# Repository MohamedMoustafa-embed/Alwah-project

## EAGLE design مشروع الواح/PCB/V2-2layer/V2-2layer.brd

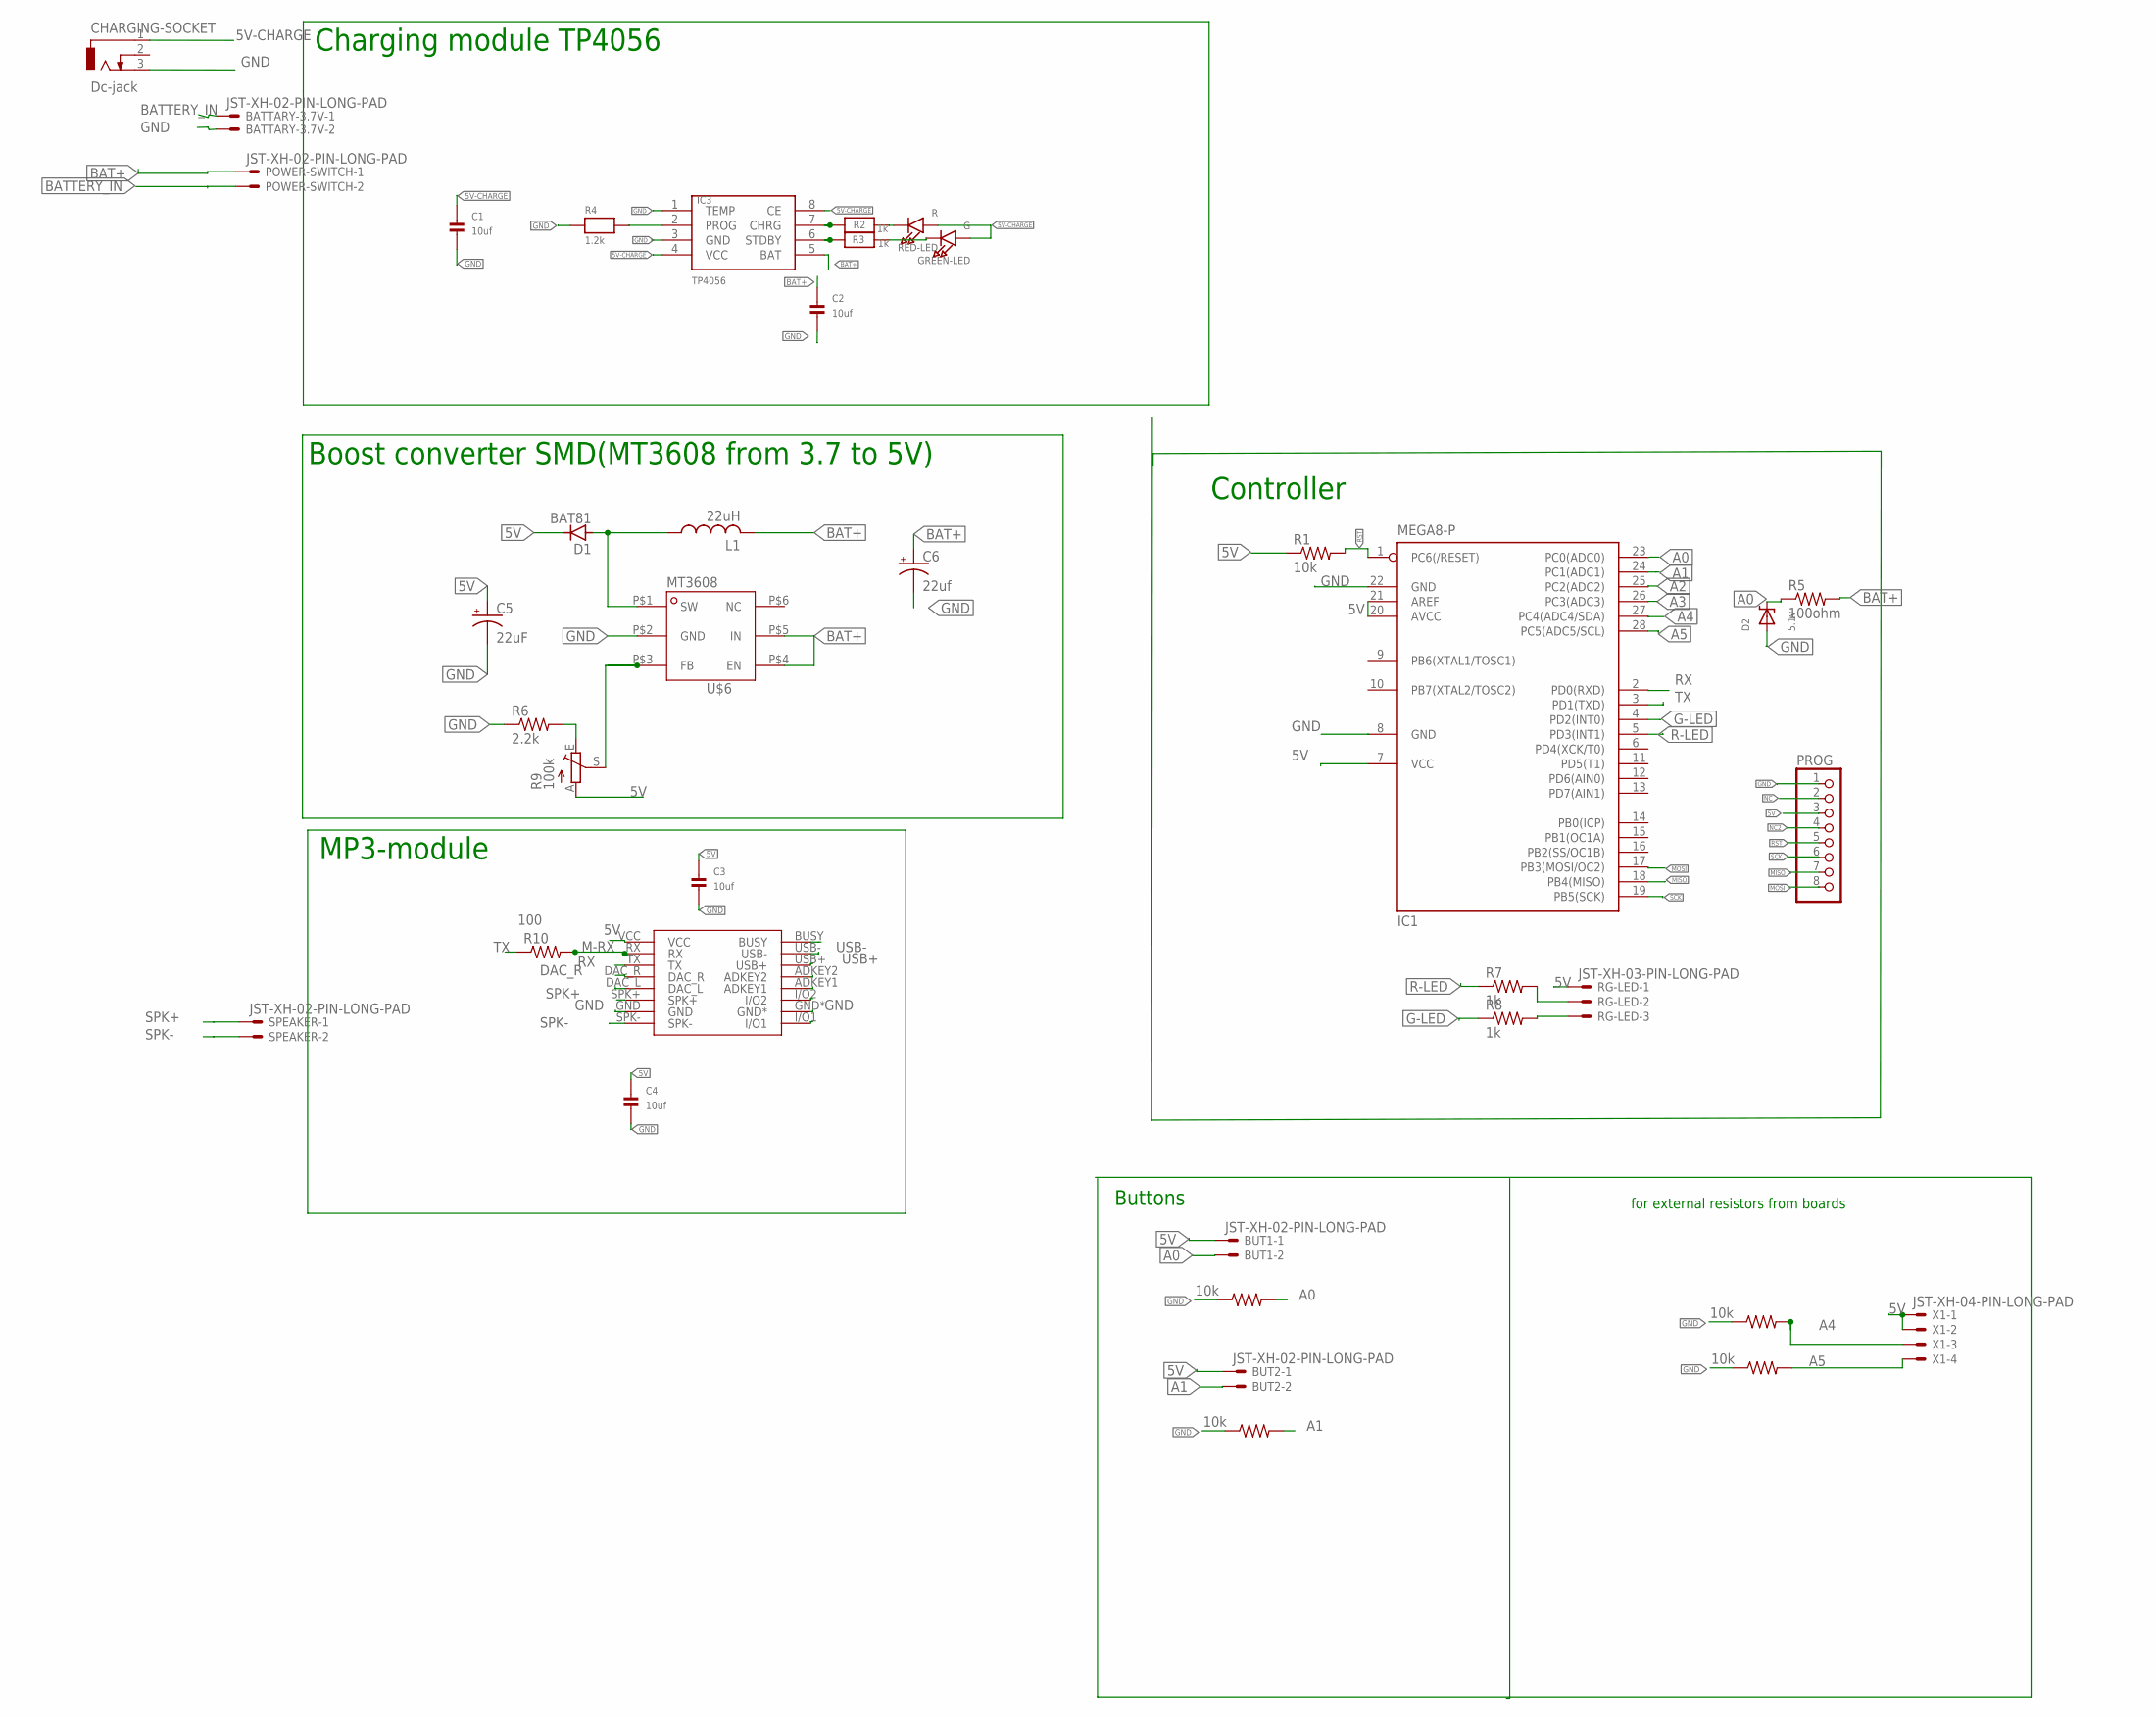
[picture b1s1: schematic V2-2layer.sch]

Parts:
BATTARY-3.7V: JST-XH-02-PIN-LONG-PAD; JST-XH-02-PACKAGE-LONG-PAD
BUT1, BUT2: JST-XH-02-PIN-LONG-PAD; JST-XH-02-PACKAGE-LONG-PAD
C1, C2, C3, C4: 10uf; 0805
C5: 22uF; E2,5-6E
C6: 22uf; E2,5-6E
CHARGING-SOCKET: Dc-jack; DCJ0303
D1: BAT81; DO34-7
D2: 5.1v; SMADIODE
GREEN-LED: G; CHIPLED_0805
IC1: MEGA8-P; DIL28-3
IC3: TP4056; SOP-8
KEYPADS, KEYPADS1, KEYPADS2, KEYPADS3: 10k; 0204/7
L1: 22uH; L1812
POWER-SWITCH: JST-XH-02-PIN-LONG-PAD; JST-XH-02-PACKAGE-LONG-PAD
PROG: PINHD-1X8; 1X08
R1: 10k; 0204/7
R2, R3: 1k; _0805
R4: 1.2k; _0805
R5: 100ohm; 0204/7
R6: 2.2k; M0805
R7, R8: 1k; 0204/7
R9: 100k; B25U
R10: 100; 0204/7
RED-LED: R; CHIPLED_0805
RG-LED: JST-XH-03-PIN-LONG-PAD; JST-XH-03-PACKAGE-LONG-PAD
SPEAKER: JST-XH-02-PIN-LONG-PAD; JST-XH-02-PACKAGE-LONG-PAD
U$2: MP3_MODULE
U$6: MT3608SOT23-6; SOT23-6
X1: JST-XH-04-PIN-LONG-PAD; JST-XH-04-PACKAGE-LONG-PAD

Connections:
5V: BUT1.1, BUT2.1, C3.1, C4.1, C5.+, D1.C, IC1.7 (VCC), IC1.20 (AVCC), IC1.21 (AREF), PROG.3, R1.1, R9.A, RG-LED.1, U$2.VCC, X1.1, X1.2
5V-CHARGE: C1.1, CHARGING-SOCKET.1, GREEN-LED.A, IC3.4 (VCC), IC3.8 (CE), RED-LED.A
A0: BUT1.2, D2.C, IC1.23 (PC0(ADC0)), KEYPADS.2, R5.1
A1: BUT2.2, IC1.24 (PC1(ADC1)), KEYPADS3.2
A2: IC1.25 (PC2(ADC2))
A3: IC1.26 (PC3(ADC3))
A4: IC1.27 (PC4(ADC4/SDA)), KEYPADS1.2, X1.3
A5: IC1.28 (PC5(ADC5/SCL)), KEYPADS2.2, X1.4
BAT+: C2.1, C6.+, IC3.5 (BAT), L1.2, POWER-SWITCH.1, R5.2, U$6.P$4 (EN), U$6.P$5 (IN)
BATTERY_IN: BATTARY-3.7V.1, POWER-SWITCH.2
DAC_L: U$2.DAC_L
DAC_R: U$2.DAC_R
G-LED: IC1.4 (PD2(INT0)), R8.1
GND: BATTARY-3.7V.2, C1.2, C2.2, C3.2, C4.2, C5.-, C6.-, CHARGING-SOCKET.3, D2.A, IC1.8 (GND), IC1.22 (GND), IC3.1 (TEMP), IC3.3 (GND), KEYPADS.1, KEYPADS1.1, KEYPADS2.1, KEYPADS3.1, PROG.1, R4.1, R6.1, U$2.GND, U$2.GND*, U$6.P$2 (GND)
M-RX: R10.2, U$2.RX
MISO: IC1.18 (PB4(MISO)), PROG.7
MOSI: IC1.17 (PB3(MOSI/OC2)), PROG.8
unnamed: IC3.2 (PROG), R4.2
unnamed: R7.2, RG-LED.2
unnamed: R8.2, RG-LED.3
unnamed: IC3.7 (CHRG), R2.1
unnamed: IC3.6 (STDBY), R3.1
unnamed: GREEN-LED.C, R3.2
unnamed: R6.2, R9.E
unnamed: R2.2, RED-LED.C
unnamed: R9.S, U$6.P$3 (FB)
unnamed: D1.A, L1.1, U$6.P$1 (SW)
NC: PROG.2
NC2: PROG.4
R-LED: IC1.5 (PD3(INT1)), R7.1
RST: IC1.1 (PC6(/RESET)), PROG.5, R1.2
RX: IC1.2 (PD0(RXD)), U$2.TX
SCK: IC1.19 (PB5(SCK)), PROG.6
SPK+: SPEAKER.1, U$2.SPK+
SPK-: SPEAKER.2, U$2.SPK-
TX: IC1.3 (PD1(TXD)), R10.1
USB+: U$2.USB+
USB-: U$2.USB-

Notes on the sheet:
Boost converter SMD(MT3608 from 3.7 to 5V)
MP3-module
Charging module TP4056
Controller
Buttons
for external resistors from boards

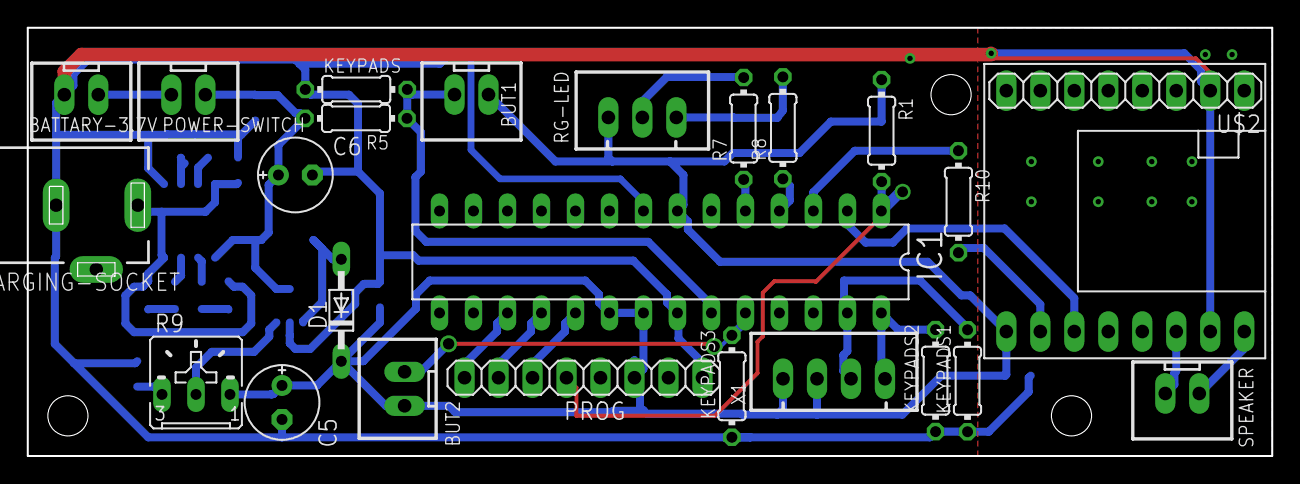
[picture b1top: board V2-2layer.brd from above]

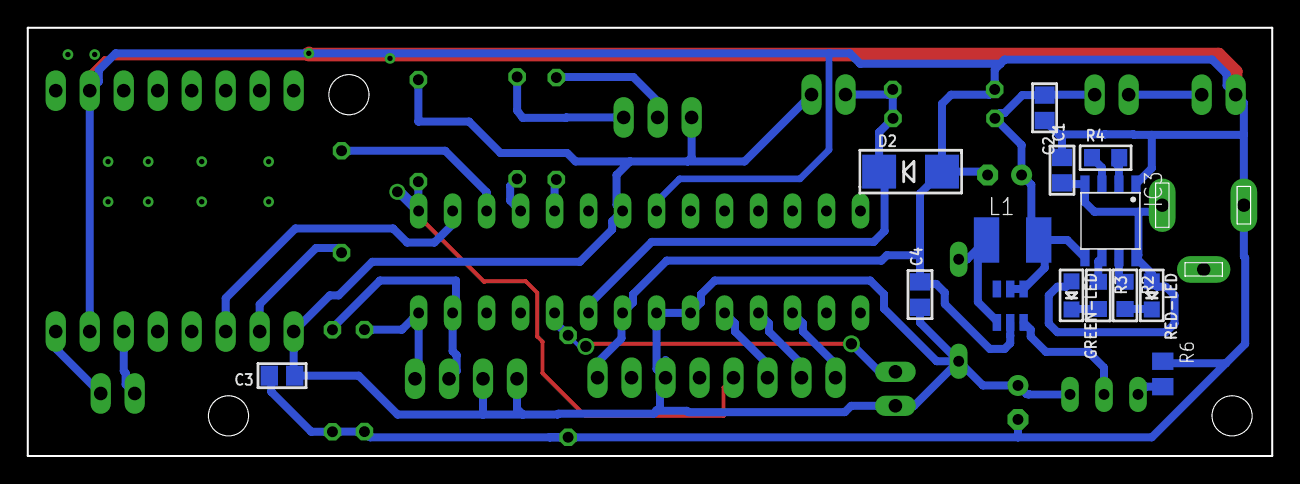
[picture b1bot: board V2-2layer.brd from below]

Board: 2 copper layers, 93.0 x 32.0 mm, 38 parts (14 on the bottom side), 30 nets.

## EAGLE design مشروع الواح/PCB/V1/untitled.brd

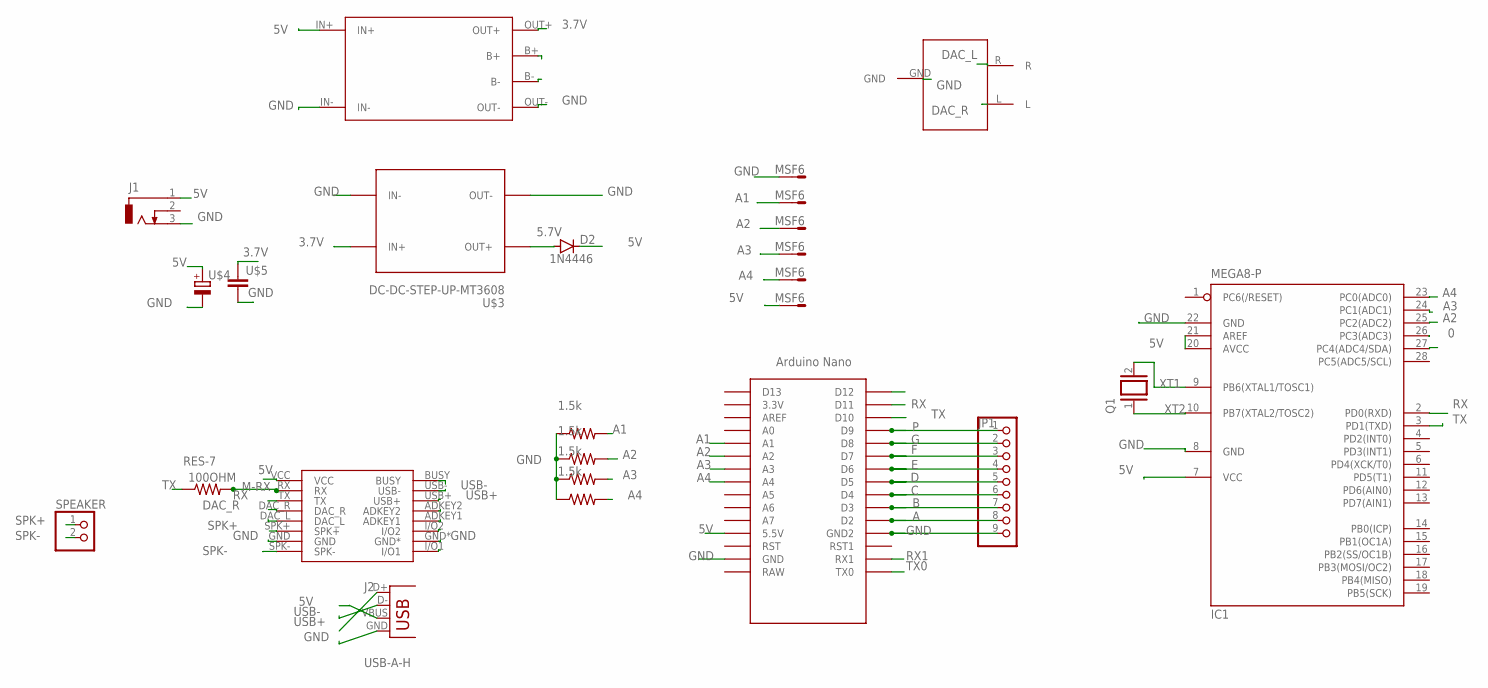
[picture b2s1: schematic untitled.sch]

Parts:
1.5K, 100OHM2, 100OHM3, 100OHM4: 1.5k; 0204/7
100OHM: RES-7; 0204/7
D2: 1N4446; DO35-10
IC1: MEGA8-P; DIL28-3
J1: CON_JACK; DCJ0303
J2: USB-A-H
JP1: PINHD-1X9; 1X09
Q1: XTAL/S; QS
SPEAKER: PINHD-1X2; 1X02
ST1: MSF6
U$1: ARDUINO_NANO; NANO
U$2: MP3_MODULE
U$3: DC-DC-STEP-UP-MT3608
U$4: CAP_POL; E3,5-8
U$5: CAPACITOR; C025-025X050
U$6: LITHIUM_CHARGER_2A; LITHIUM-CHARGER-1A
U$7: EAR-PHONE-SOCKET

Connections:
0: IC1.26 (PC3(ADC3))
3.7V: U$3.IN+, U$5.1, U$6.OUT+
5.7V: D2.A, U$3.OUT+
5V: D2.C, IC1.7 (VCC), IC1.20 (AVCC), IC1.21 (AREF), J1.1, J2.VBUS, ST1.1, U$1.5V (5.5V), U$2.VCC, U$4.+, U$6.IN+
A: JP1.8, U$1.D2
A1: 1.5K.2, ST1.5, U$1.A1
A2: 100OHM2.2, IC1.25 (PC2(ADC2)), ST1.4, U$1.A2
A3: 100OHM3.2, IC1.24 (PC1(ADC1)), ST1.3, U$1.A3
A4: 100OHM4.2, IC1.23 (PC0(ADC0)), ST1.2, U$1.A4
B: JP1.7, U$1.D3
C: JP1.6, U$1.D4
D: JP1.5, U$1.D5
DAC_L: U$2.DAC_L, U$7.R
DAC_R: U$2.DAC_R, U$7.L
E: JP1.4, U$1.D6
F: JP1.3, U$1.D7
G: JP1.2, U$1.D8
GND: 1.5K.1, 100OHM2.1, 100OHM3.1, 100OHM4.1, IC1.8 (GND), IC1.22 (GND), J1.3, J2.GND, JP1.9, ST1.6, U$1.GND, U$1.GND1 (GND2), U$2.GND, U$2.GND*, U$3.IN-, U$3.OUT-, U$4.-, U$5.2, U$6.IN-, U$6.OUT-, U$7.GND
M-RX: 100OHM.2, U$2.RX
P: JP1.1, U$1.D9
RX: IC1.2 (PD0(RXD)), U$1.D11, U$2.TX
RX1: U$1.RX1
SPK+: SPEAKER.1, U$2.SPK+
SPK-: SPEAKER.2, U$2.SPK-
TX: 100OHM.1, IC1.3 (PD1(TXD)), U$1.D10
TX0: U$1.TX0
USB+: J2.D+, U$2.USB+
USB-: J2.D-, U$2.USB-
XT1: IC1.9 (PB6(XTAL1/TOSC1)), Q1.2
XT2: IC1.10 (PB7(XTAL2/TOSC2)), Q1.1

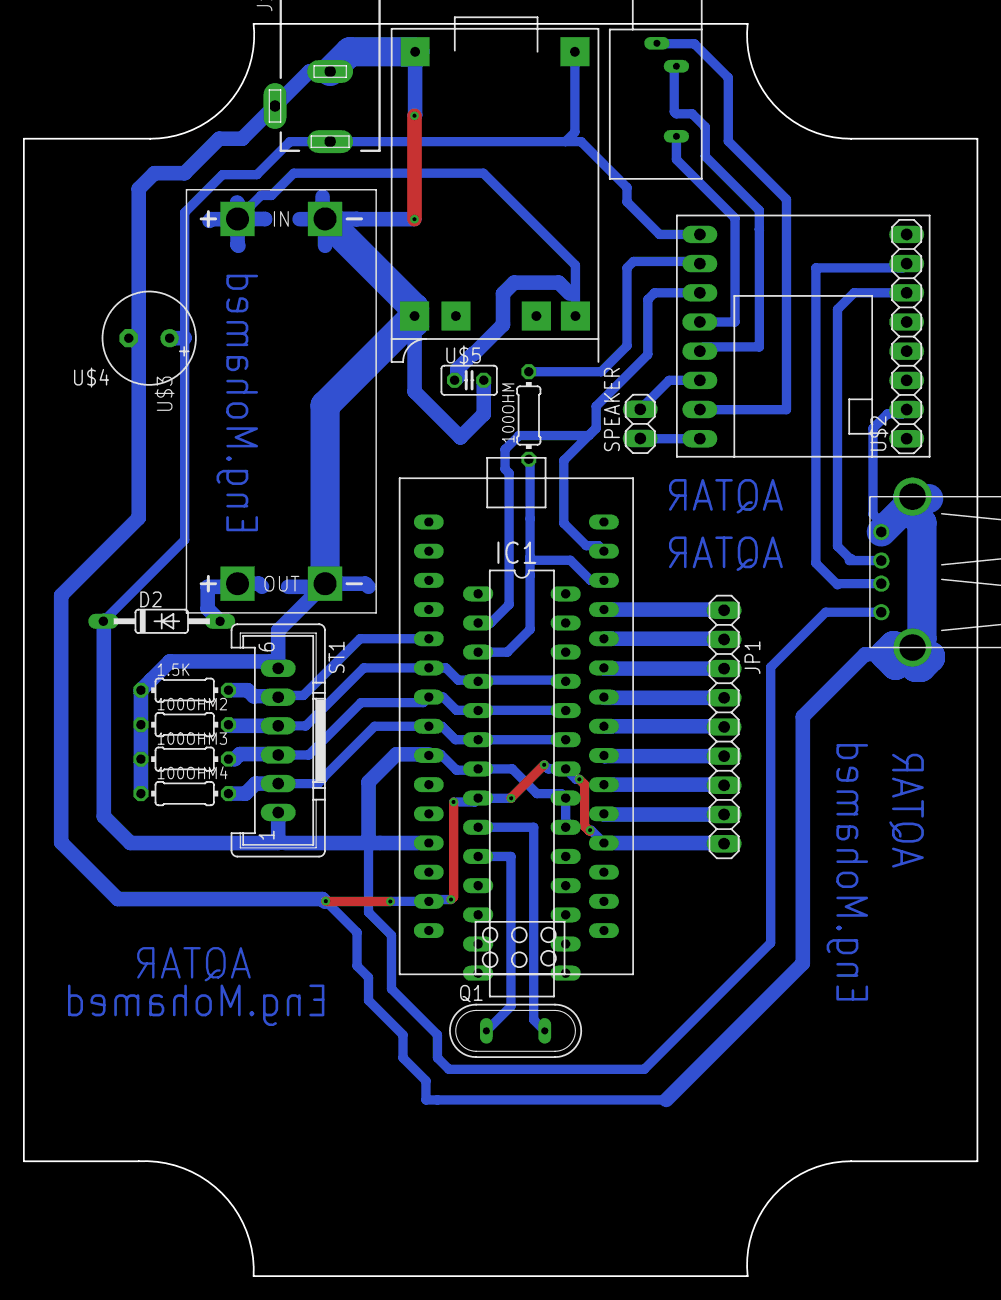
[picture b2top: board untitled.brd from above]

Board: 2 copper layers, 83.0 x 109.0 mm, 20 parts (0 on the bottom side), 27 nets.

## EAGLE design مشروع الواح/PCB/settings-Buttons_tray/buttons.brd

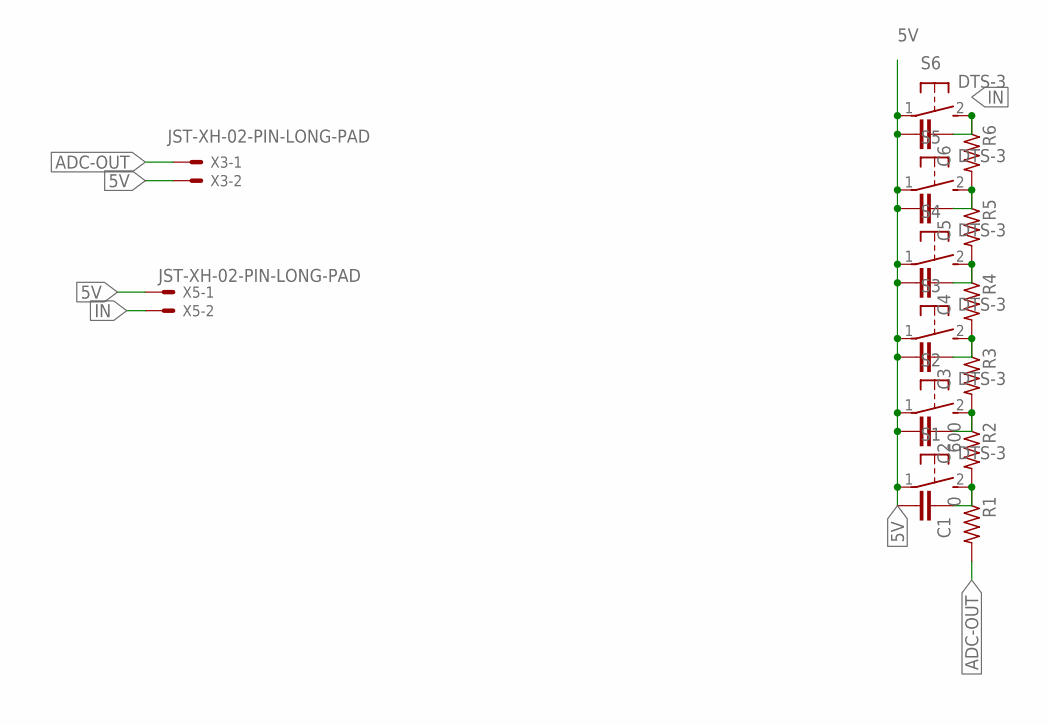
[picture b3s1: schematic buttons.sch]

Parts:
C1, C2, C3, C4, C5, C6: C-EU025-024X044; C025-024X044
R1: 0; 0204/7
R2: 600; 0204/7
R3, R4, R5, R6: R-US_0204/7; 0204/7
S1, S2, S3, S4, S5, S6: DTS-3
X3, X5: JST-XH-02-PIN-LONG-PAD; JST-XH-02-PACKAGE-LONG-PAD

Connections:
5V: C1.2, C2.2, C3.2, C4.2, C5.2, C6.2, S1.1, S2.1, S3.1, S4.1, S5.1, S6.1, X3.2, X5.1
ADC-OUT: R1.2, X3.1
IN: C6.1, R6.1, S6.2, X5.2
unnamed: C1.1, R1.1, R2.2, S1.2
unnamed: C2.1, R2.1, R3.2, S2.2
unnamed: C3.1, R3.1, R4.2, S3.2
unnamed: C4.1, R4.1, R5.2, S4.2
unnamed: C5.1, R5.1, R6.2, S5.2

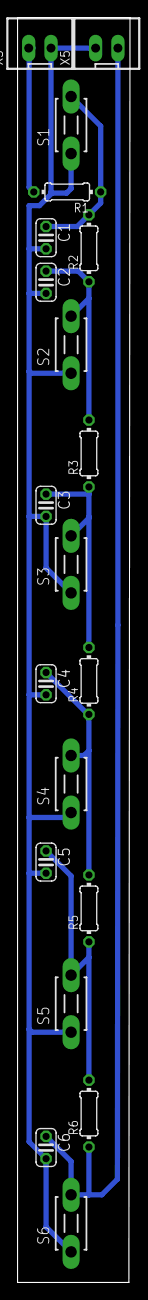
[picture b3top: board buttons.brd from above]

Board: 2 copper layers, 12.8 x 144.1 mm, 20 parts (0 on the bottom side), 8 nets.

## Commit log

2022-01-04 uploaf
2022-01-04 upload
2022-02-24 eddit design
2022-02-24 edit pcb design

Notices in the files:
parts and their libraries:
microbuilder: This work is placed in the public domain, and may be freely used for commercial and non-commercial work with the following conditions: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
